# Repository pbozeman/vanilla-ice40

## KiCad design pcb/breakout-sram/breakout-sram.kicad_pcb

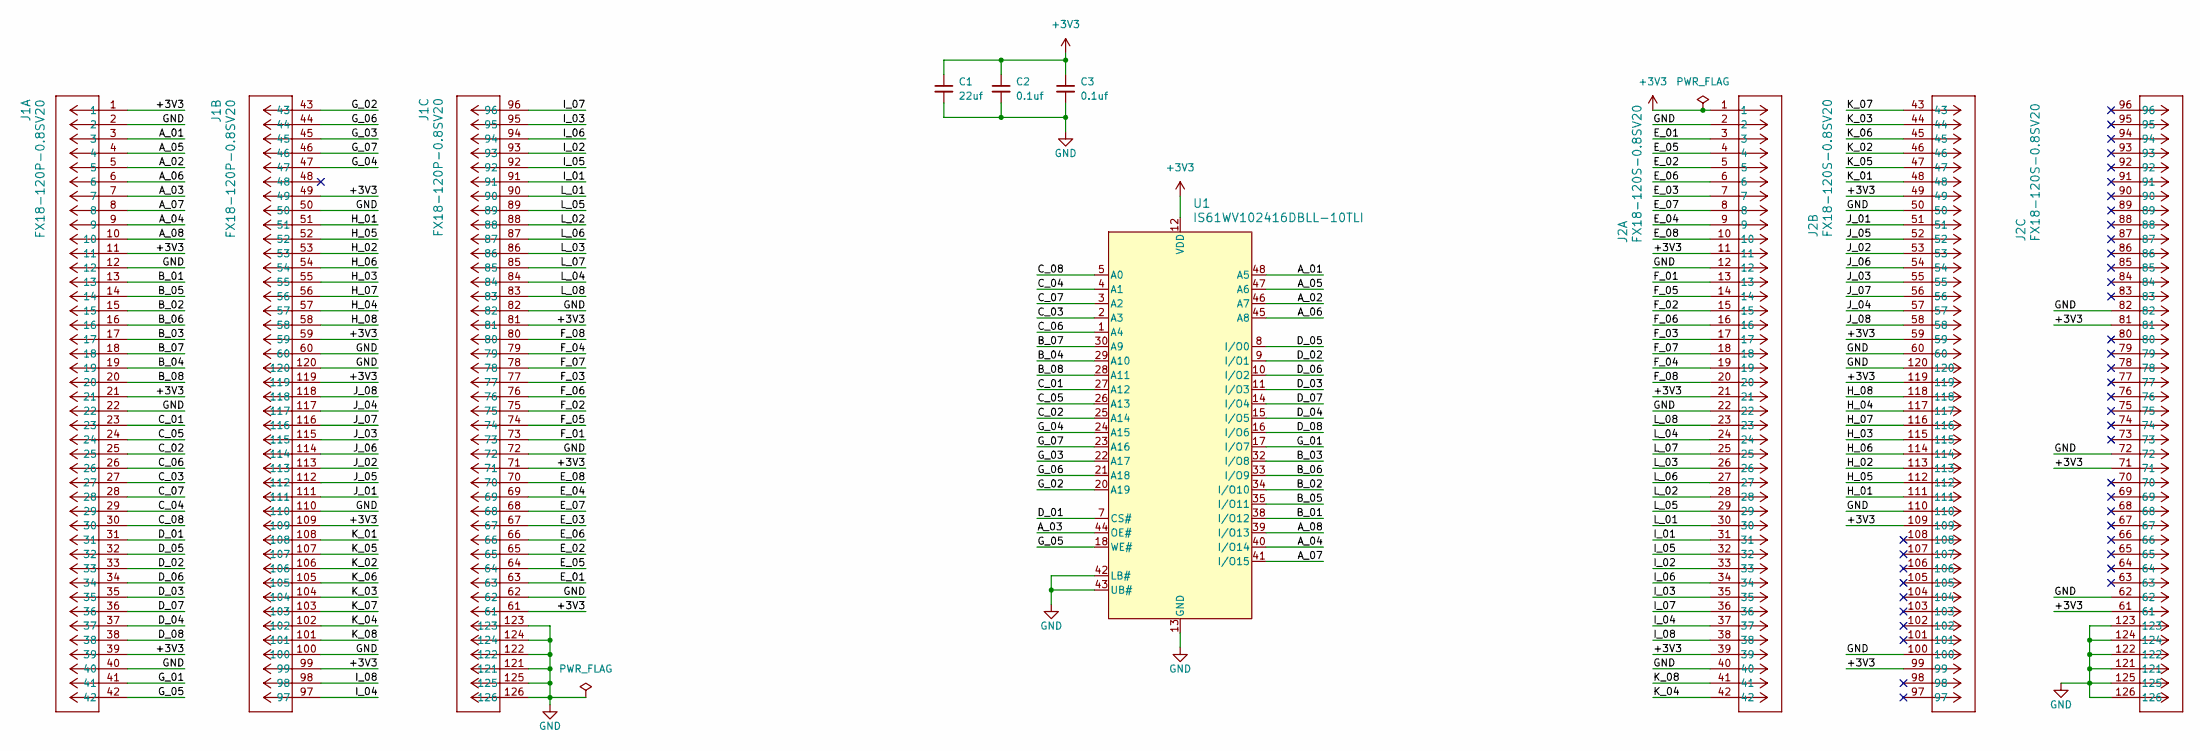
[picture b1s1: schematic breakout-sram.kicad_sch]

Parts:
C1: 22uf; C_0603_1608Metric; LCSC Part # C59461
C2, C3: 0.1uf; C_0402_1005Metric; LCSC Part # C1525
J1: FX18-120P-0.8SV20; CUSTOM_FX_120P-0.8SH20; Digi-Key Part Number H11865-ND
J2: FX18-120S-0.8SV20; CUSTOM_FX_120S-0.8SH20; Digi-Key Part Number H11867-ND
U1: IS61WV102416DBLL-10TLI; IS61WV102416DBLL-10TLI_ISI; LCSC Part # C1348726

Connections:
+3V3: C1.1, C2.1, C3.1, J1.1, J1.11, J1.21, J1.39, J1.49, J1.59, J1.61, J1.71, J1.81, J1.99, J1.109, J1.119, J2.1, J2.11, J2.21, J2.39, J2.49, J2.59, J2.61, J2.71, J2.81, J2.99, J2.109, J2.119, U1.12 (VDD), U1.36 (VDD)
/A_01: J1.3, U1.48 (A5)
/A_02: J1.5, U1.46 (A7)
/A_03: J1.7, U1.44 (OE#)
/A_04: J1.9, U1.40 (I/O14)
/A_05: J1.4, U1.47 (A6)
/A_06: J1.6, U1.45 (A8)
/A_07: J1.8, U1.41 (I/O15)
/A_08: J1.10, U1.39 (I/O13)
/B_01: J1.13, U1.38 (I/O12)
/B_02: J1.15, U1.34 (I/O10)
/B_03: J1.17, U1.32 (I/O8)
/B_04: J1.19, U1.29 (A10)
/B_05: J1.14, U1.35 (I/O11)
/B_06: J1.16, U1.33 (I/O9)
/B_07: J1.18, U1.30 (A9)
/B_08: J1.20, U1.28 (A11)
/C_01: J1.23, U1.27 (A12)
/C_02: J1.25, U1.25 (A14)
/C_03: J1.27, U1.2 (A3)
/C_04: J1.29, U1.4 (A1)
/C_05: J1.24, U1.26 (A13)
/C_06: J1.26, U1.1 (A4)
/C_07: J1.28, U1.3 (A2)
/C_08: J1.30, U1.5 (A0)
/D_01: J1.31, U1.7 (CS#)
/D_02: J1.33, U1.9 (I/O1)
/D_03: J1.35, U1.11 (I/O3)
/D_04: J1.37, U1.15 (I/O5)
/D_05: J1.32, U1.8 (I/O0)
/D_06: J1.34, U1.10 (I/O2)
/D_07: J1.36, U1.14 (I/O4)
/D_08: J1.38, U1.16 (I/O6)
/E_01: J1.63, J2.3
/E_02: J1.65, J2.5
/E_03: J1.67, J2.7
/E_04: J1.69, J2.9
/E_05: J1.64, J2.4
/E_06: J1.66, J2.6
/E_07: J1.68, J2.8
/E_08: J1.70, J2.10
/F_01: J1.73, J2.13
/F_02: J1.75, J2.15
/F_03: J1.77, J2.17
/F_04: J1.79, J2.19
/F_05: J1.74, J2.14
/F_06: J1.76, J2.16
/F_07: J1.78, J2.18
/F_08: J1.80, J2.20
/G_01: J1.41, U1.17 (I/O7)
/G_02: J1.43, U1.20 (A19)
/G_03: J1.45, U1.22 (A17)
/G_04: J1.47, U1.24 (A15)
/G_05: J1.42, U1.18 (WE#)
/G_06: J1.44, U1.21 (A18)
/G_07: J1.46, U1.23 (A16)
/H_01: J1.51, J2.111
/H_02: J1.53, J2.113
/H_03: J1.55, J2.115
/H_04: J1.57, J2.117
/H_05: J1.52, J2.112
/H_06: J1.54, J2.114
/H_07: J1.56, J2.116
/H_08: J1.58, J2.118
/I_01: J1.91, J2.31
/I_02: J1.93, J2.33
/I_03: J1.95, J2.35
/I_04: J1.97, J2.37
/I_05: J1.92, J2.32
/I_06: J1.94, J2.34
/I_07: J1.96, J2.36
/I_08: J1.98, J2.38
/J_01: J1.111, J2.51
/J_02: J1.113, J2.53
/J_03: J1.115, J2.55
/J_04: J1.117, J2.57
/J_05: J1.112, J2.52
/J_06: J1.114, J2.54
/J_07: J1.116, J2.56
/J_08: J1.118, J2.58
/K_01: J1.108, J2.48
/K_02: J1.106, J2.46
/K_03: J1.104, J2.44
/K_04: J1.102, J2.42
/K_05: J1.107, J2.47
/K_06: J1.105, J2.45
/K_07: J1.103, J2.43
/K_08: J1.101, J2.41
/L_01: J1.90, J2.30
/L_02: J1.88, J2.28
/L_03: J1.86, J2.26
/L_04: J1.84, J2.24
/L_05: J1.89, J2.29
/L_06: J1.87, J2.27
/L_07: J1.85, J2.25
/L_08: J1.83, J2.23
GND: C1.2, C2.2, C3.2, J1.2, J1.12, J1.22, J1.40, J1.50, J1.60, J1.62, J1.72, J1.82, J1.100, J1.110, J1.120, J1.121, J1.122, J1.123, J1.124, J1.125, J1.126, J2.2, J2.12, J2.22, J2.40, J2.50, J2.60, J2.62, J2.72, J2.82, J2.100, J2.110, J2.120, J2.121, J2.122, J2.123, J2.124, J2.125, J2.126, U1.13 (GND), U1.37 (GND), U1.42 (LB#), U1.43 (UB#)

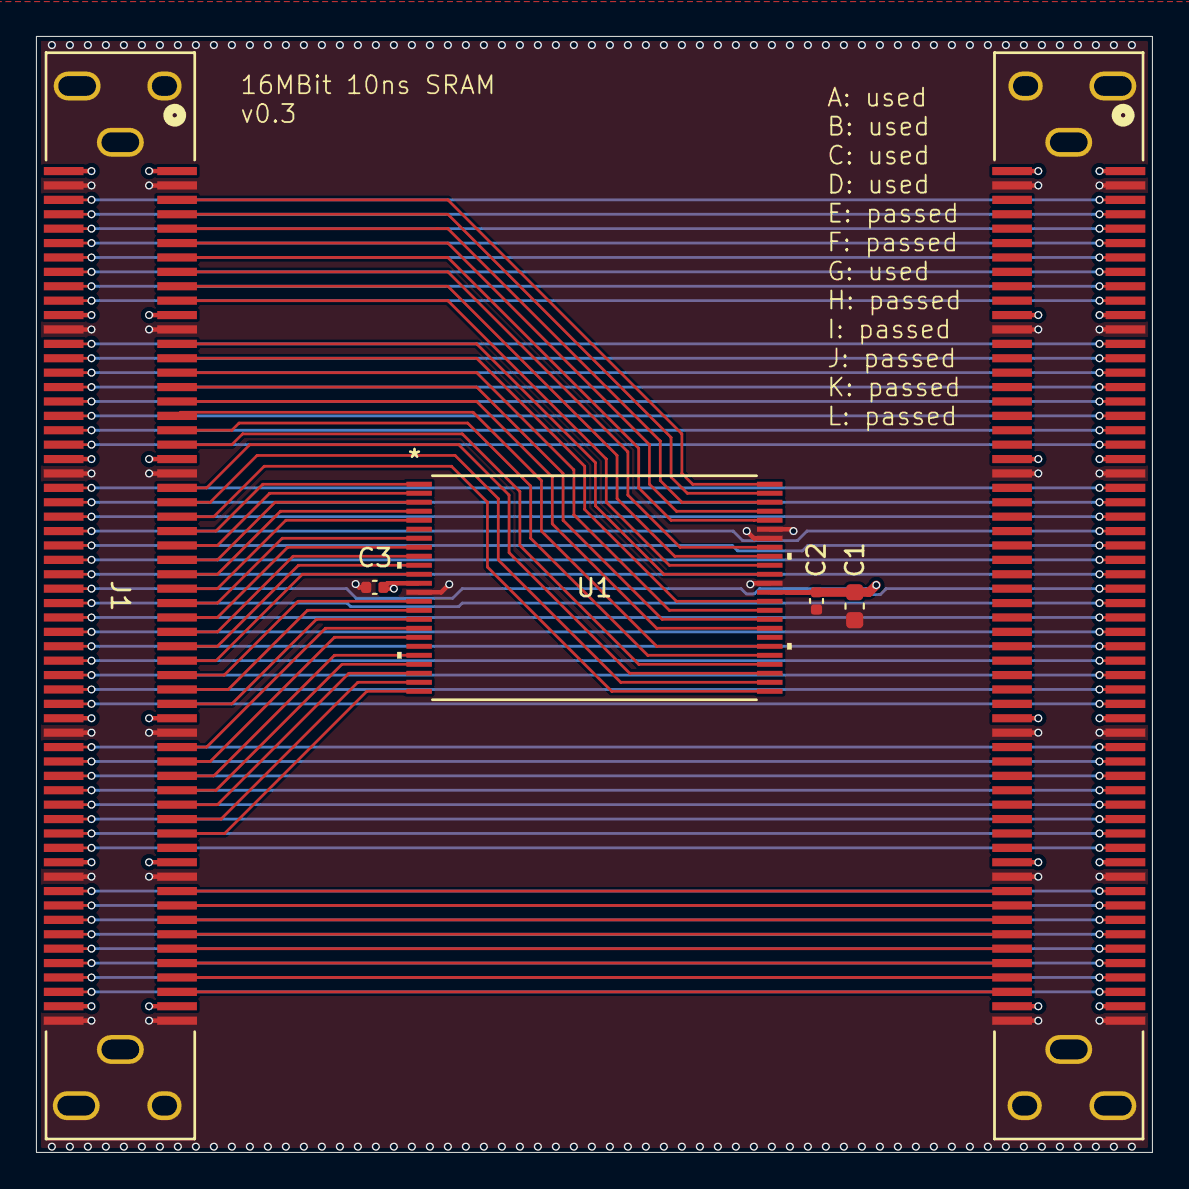
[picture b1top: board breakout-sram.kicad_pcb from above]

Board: 4 copper layers, 62.0 x 62.0 mm, 6 parts (0 on the bottom side), 97 nets.

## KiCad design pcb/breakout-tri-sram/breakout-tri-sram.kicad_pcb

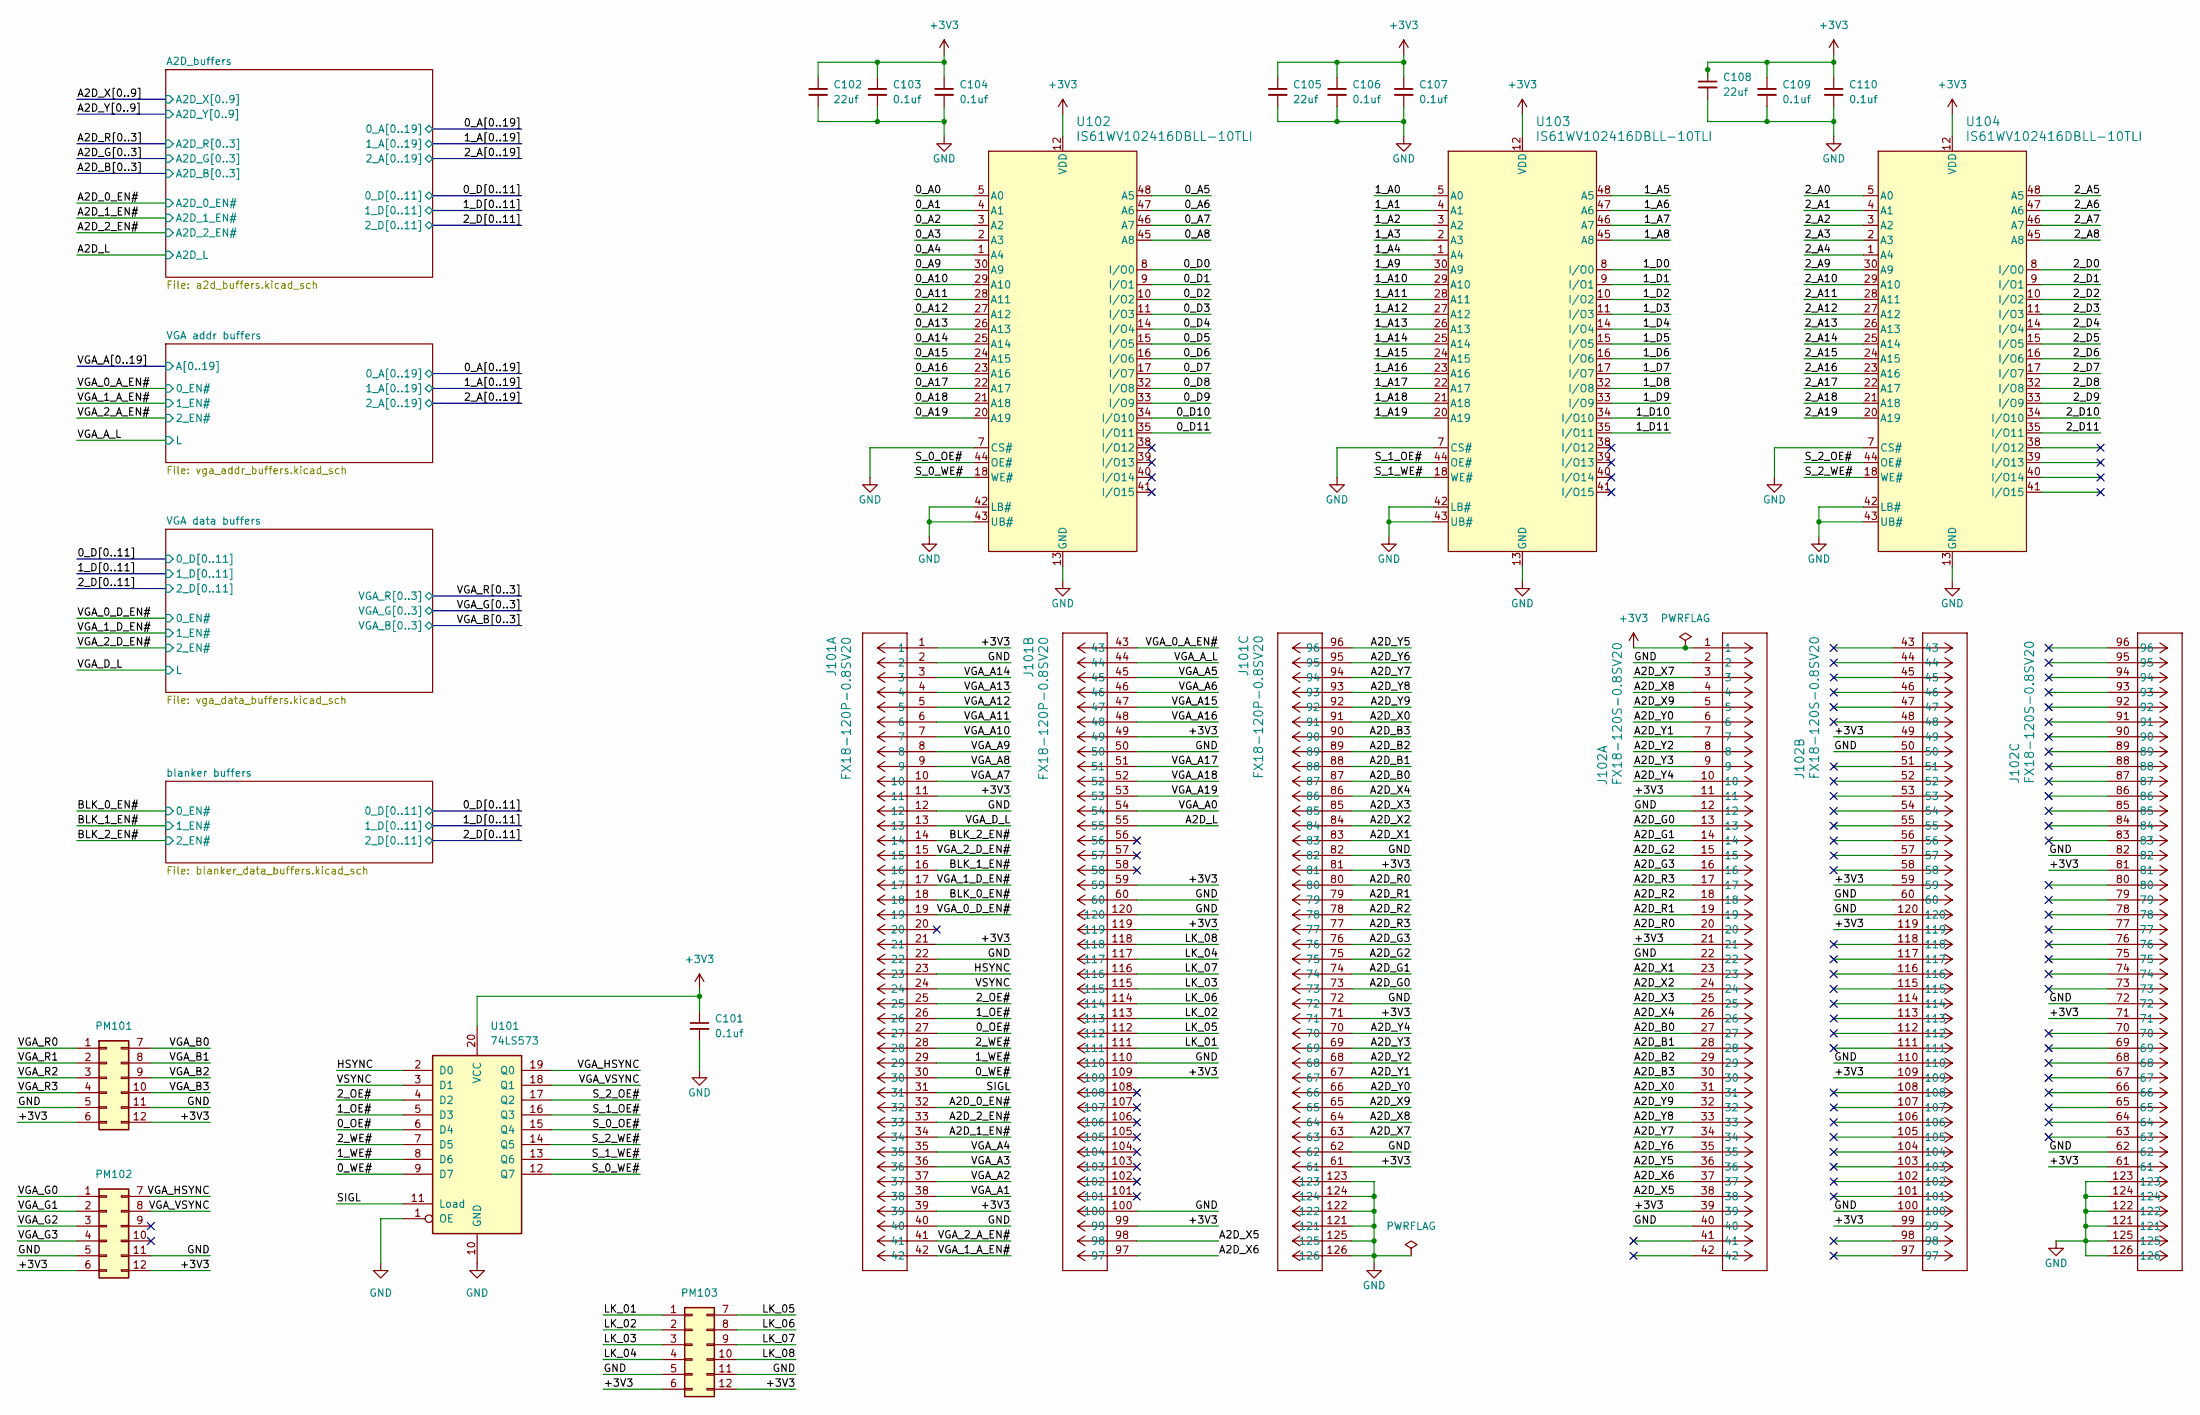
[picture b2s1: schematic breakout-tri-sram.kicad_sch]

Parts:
C101, C103, C104, C106, C107, C109, C110: 0.1uf; C_0402_1005Metric; LCSC Part # C1525
C102, C105, C108: 22uf; C_0603_1608Metric; LCSC Part # C59461
J101: FX18-120P-0.8SV20; CUSTOM_FX_120S-0.8SH20; Digi-Key Part Number H11865-ND
J102: FX18-120S-0.8SV20; CUSTOM_FX_120S-0.8SH20; Digi-Key Part Number H11867-ND
PM101, PM102, PM103: Conn_02x06_Top_Bottom; PMOD_12p_Horizontal; Digi-Key Part Number S5559-ND
U101: 74LS573; SSOP-20_4.4x6.5mm_P0.65mm; LCSC Part # C7194124
U102, U103, U104: IS61WV102416DBLL-10TLI; IS61WV102416DBLL-10TLI_ISI; LCSC Part # C1348726

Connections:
+3V3: C101.1, C102.1, C103.1, C104.1, C105.1, C106.1, C107.1, C108.1, C109.1, C110.1, J101.1, J101.11, J101.21, J101.39, J101.49, J101.59, J101.61, J101.71, J101.81, J101.99, J101.109, J101.119, J102.1, J102.11, J102.21, J102.39, J102.49, J102.59, J102.61, J102.71, J102.81, J102.99, J102.109, J102.119, PM101.6, PM101.12, PM102.6, PM102.12, PM103.6, PM103.12, U101.20 (VCC), U102.12 (VDD), U102.36 (VDD), U103.12 (VDD), U103.36 (VDD), U104.12 (VDD), U104.36 (VDD); also elsewhere on the board
/0_A0: U102.5 (A0); also elsewhere on the board
/0_A1: U102.4 (A1); also elsewhere on the board
/0_A2: U102.3 (A2); also elsewhere on the board
/0_A3: U102.2 (A3); also elsewhere on the board
/0_A4: U102.1 (A4); also elsewhere on the board
/0_A5: U102.48 (A5); also elsewhere on the board
/0_A6: U102.47 (A6); also elsewhere on the board
/0_A7: U102.46 (A7); also elsewhere on the board
/0_A8: U102.45 (A8); also elsewhere on the board
/0_A9: U102.30 (A9); also elsewhere on the board
/0_A10: U102.29 (A10); also elsewhere on the board
/0_A11: U102.28 (A11); also elsewhere on the board
/0_A12: U102.27 (A12); also elsewhere on the board
/0_A13: U102.26 (A13); also elsewhere on the board
/0_A14: U102.25 (A14); also elsewhere on the board
/0_A15: U102.24 (A15); also elsewhere on the board
/0_A16: U102.23 (A16); also elsewhere on the board
/0_A17: U102.22 (A17); also elsewhere on the board
/0_A18: U102.21 (A18); also elsewhere on the board
/0_A19: U102.20 (A19); also elsewhere on the board
/0_D0: U102.8 (I/O0); also elsewhere on the board
/0_D1: U102.9 (I/O1); also elsewhere on the board
/0_D2: U102.10 (I/O2); also elsewhere on the board
/0_D3: U102.11 (I/O3); also elsewhere on the board
/0_D4: U102.14 (I/O4); also elsewhere on the board
/0_D5: U102.15 (I/O5); also elsewhere on the board
/0_D6: U102.16 (I/O6); also elsewhere on the board
/0_D7: U102.17 (I/O7); also elsewhere on the board
/0_D8: U102.32 (I/O8); also elsewhere on the board
/0_D9: U102.33 (I/O9); also elsewhere on the board
/0_D10: U102.34 (I/O10); also elsewhere on the board
/0_D11: U102.35 (I/O11); also elsewhere on the board
/0_OE#: J101.27, U101.6 (D4)
/0_WE#: J101.30, U101.9 (D7)
/1_A0: U103.5 (A0); also elsewhere on the board
/1_A1: U103.4 (A1); also elsewhere on the board
/1_A2: U103.3 (A2); also elsewhere on the board
/1_A3: U103.2 (A3); also elsewhere on the board
/1_A4: U103.1 (A4); also elsewhere on the board
/1_A5: U103.48 (A5); also elsewhere on the board
/1_A6: U103.47 (A6); also elsewhere on the board
/1_A7: U103.46 (A7); also elsewhere on the board
/1_A8: U103.45 (A8); also elsewhere on the board
/1_A9: U103.30 (A9); also elsewhere on the board
/1_A10: U103.29 (A10); also elsewhere on the board
/1_A11: U103.28 (A11); also elsewhere on the board
/1_A12: U103.27 (A12); also elsewhere on the board
/1_A13: U103.26 (A13); also elsewhere on the board
/1_A14: U103.25 (A14); also elsewhere on the board
/1_A15: U103.24 (A15); also elsewhere on the board
/1_A16: U103.23 (A16); also elsewhere on the board
/1_A17: U103.22 (A17); also elsewhere on the board
/1_A18: U103.21 (A18); also elsewhere on the board
/1_A19: U103.20 (A19); also elsewhere on the board
/1_D0: U103.8 (I/O0); also elsewhere on the board
/1_D1: U103.9 (I/O1); also elsewhere on the board
/1_D2: U103.10 (I/O2); also elsewhere on the board
/1_D3: U103.11 (I/O3); also elsewhere on the board
/1_D4: U103.14 (I/O4); also elsewhere on the board
/1_D5: U103.15 (I/O5); also elsewhere on the board
/1_D6: U103.16 (I/O6); also elsewhere on the board
/1_D7: U103.17 (I/O7); also elsewhere on the board
/1_D8: U103.32 (I/O8); also elsewhere on the board
/1_D9: U103.33 (I/O9); also elsewhere on the board
/1_D10: U103.34 (I/O10); also elsewhere on the board
/1_D11: U103.35 (I/O11); also elsewhere on the board
/1_OE#: J101.26, U101.5 (D3)
/1_WE#: J101.29, U101.8 (D6)
/2_A0: U104.5 (A0); also elsewhere on the board
/2_A1: U104.4 (A1); also elsewhere on the board
/2_A2: U104.3 (A2); also elsewhere on the board
/2_A3: U104.2 (A3); also elsewhere on the board
/2_A4: U104.1 (A4); also elsewhere on the board
/2_A5: U104.48 (A5); also elsewhere on the board
/2_A6: U104.47 (A6); also elsewhere on the board
/2_A7: U104.46 (A7); also elsewhere on the board
/2_A8: U104.45 (A8); also elsewhere on the board
/2_A9: U104.30 (A9); also elsewhere on the board
/2_A10: U104.29 (A10); also elsewhere on the board
/2_A11: U104.28 (A11); also elsewhere on the board
/2_A12: U104.27 (A12); also elsewhere on the board
/2_A13: U104.26 (A13); also elsewhere on the board
/2_A14: U104.25 (A14); also elsewhere on the board
/2_A15: U104.24 (A15); also elsewhere on the board
/2_A16: U104.23 (A16); also elsewhere on the board
/2_A17: U104.22 (A17); also elsewhere on the board
/2_A18: U104.21 (A18); also elsewhere on the board
/2_A19: U104.20 (A19); also elsewhere on the board
/2_D0: U104.8 (I/O0); also elsewhere on the board
/2_D1: U104.9 (I/O1); also elsewhere on the board
/2_D2: U104.10 (I/O2); also elsewhere on the board
/2_D3: U104.11 (I/O3); also elsewhere on the board
/2_D4: U104.14 (I/O4); also elsewhere on the board
/2_D5: U104.15 (I/O5); also elsewhere on the board
/2_D6: U104.16 (I/O6); also elsewhere on the board
/2_D7: U104.17 (I/O7); also elsewhere on the board
/2_D8: U104.32 (I/O8); also elsewhere on the board
/2_D9: U104.33 (I/O9); also elsewhere on the board
/2_D10: U104.34 (I/O10); also elsewhere on the board
/2_D11: U104.35 (I/O11); also elsewhere on the board
/2_OE#: J101.25, U101.4 (D2)
/2_WE#: J101.28, U101.7 (D5)
/A2D_0_EN#: J101.32; also elsewhere on the board
/A2D_1_EN#: J101.34; also elsewhere on the board
/A2D_2_EN#: J101.33; also elsewhere on the board
/A2D_B0: J101.87, J102.27; also elsewhere on the board
/A2D_B1: J101.88, J102.28; also elsewhere on the board
/A2D_B2: J101.89, J102.29; also elsewhere on the board
/A2D_B3: J101.90, J102.30; also elsewhere on the board
/A2D_G0: J101.73, J102.13; also elsewhere on the board
/A2D_G1: J101.74, J102.14; also elsewhere on the board
/A2D_G2: J101.75, J102.15; also elsewhere on the board
/A2D_G3: J101.76, J102.16; also elsewhere on the board
/A2D_L: J101.55; also elsewhere on the board
/A2D_R0: J101.80, J102.20; also elsewhere on the board
/A2D_R1: J101.79, J102.19; also elsewhere on the board
/A2D_R2: J101.78, J102.18; also elsewhere on the board
/A2D_R3: J101.77, J102.17; also elsewhere on the board
/A2D_X0: J101.91, J102.31; also elsewhere on the board
/A2D_X1: J101.83, J102.23; also elsewhere on the board
/A2D_X2: J101.84, J102.24; also elsewhere on the board
/A2D_X3: J101.85, J102.25; also elsewhere on the board
/A2D_X4: J101.86, J102.26; also elsewhere on the board
/A2D_X5: J101.98, J102.38; also elsewhere on the board
/A2D_X6: J101.97, J102.37; also elsewhere on the board
/A2D_X7: J101.63, J102.3; also elsewhere on the board
/A2D_X8: J101.64, J102.4; also elsewhere on the board
/A2D_X9: J101.65, J102.5; also elsewhere on the board
/A2D_Y0: J101.66, J102.6; also elsewhere on the board
/A2D_Y1: J101.67, J102.7; also elsewhere on the board
/A2D_Y2: J101.68, J102.8; also elsewhere on the board
/A2D_Y3: J101.69, J102.9; also elsewhere on the board
/A2D_Y4: J101.70, J102.10; also elsewhere on the board
/A2D_Y5: J101.96, J102.36; also elsewhere on the board
/A2D_Y6: J101.95, J102.35; also elsewhere on the board
/A2D_Y7: J101.94, J102.34; also elsewhere on the board
/A2D_Y8: J101.93, J102.33; also elsewhere on the board
/A2D_Y9: J101.92, J102.32; also elsewhere on the board
/BLK_0_EN#: J101.18; also elsewhere on the board
/BLK_1_EN#: J101.16; also elsewhere on the board
/BLK_2_EN#: J101.14; also elsewhere on the board
/HSYNC: J101.23, U101.2 (D0)
/LK_01: J101.111, PM103.1
/LK_02: J101.113, PM103.2
/LK_03: J101.115, PM103.3
/LK_04: J101.117, PM103.4
/LK_05: J101.112, PM103.7
/LK_06: J101.114, PM103.8
/LK_07: J101.116, PM103.9
/LK_08: J101.118, PM103.10
/SIGL: J101.31, U101.11 (Load)
/S_0_OE#: U101.15 (Q4), U102.44 (OE#)
/S_0_WE#: U101.12 (Q7), U102.18 (WE#)
/S_1_OE#: U101.16 (Q3), U103.44 (OE#)
/S_1_WE#: U101.13 (Q6), U103.18 (WE#)
/S_2_OE#: U101.17 (Q2), U104.44 (OE#)
/S_2_WE#: U101.14 (Q5), U104.18 (WE#)
/VGA_0_A_EN#: J101.43; also elsewhere on the board
/VGA_0_D_EN#: J101.19; also elsewhere on the board
/VGA_1_A_EN#: J101.42; also elsewhere on the board
/VGA_1_D_EN#: J101.17; also elsewhere on the board
/VGA_2_A_EN#: J101.41; also elsewhere on the board
/VGA_2_D_EN#: J101.15; also elsewhere on the board
/VGA_A0: J101.54; also elsewhere on the board
/VGA_A1: J101.38; also elsewhere on the board
/VGA_A2: J101.37; also elsewhere on the board
/VGA_A3: J101.36; also elsewhere on the board
/VGA_A4: J101.35; also elsewhere on the board
/VGA_A5: J101.45; also elsewhere on the board
/VGA_A6: J101.46; also elsewhere on the board
/VGA_A7: J101.10; also elsewhere on the board
/VGA_A8: J101.9; also elsewhere on the board
/VGA_A9: J101.8; also elsewhere on the board
/VGA_A10: J101.7; also elsewhere on the board
/VGA_A11: J101.6; also elsewhere on the board
/VGA_A12: J101.5; also elsewhere on the board
/VGA_A13: J101.4; also elsewhere on the board
/VGA_A14: J101.3; also elsewhere on the board
/VGA_A15: J101.47; also elsewhere on the board
/VGA_A16: J101.48; also elsewhere on the board
/VGA_A17: J101.51; also elsewhere on the board
/VGA_A18: J101.52; also elsewhere on the board
/VGA_A19: J101.53; also elsewhere on the board
/VGA_A_L: J101.44; also elsewhere on the board
/VGA_B0: PM101.7; also elsewhere on the board
/VGA_B1: PM101.8; also elsewhere on the board
/VGA_B2: PM101.9; also elsewhere on the board
/VGA_B3: PM101.10; also elsewhere on the board
/VGA_D_L: J101.13; also elsewhere on the board
/VGA_G0: PM102.1; also elsewhere on the board
/VGA_G1: PM102.2; also elsewhere on the board
/VGA_G2: PM102.3; also elsewhere on the board
/VGA_G3: PM102.4; also elsewhere on the board
/VGA_HSYNC: PM102.7, U101.19 (Q0)
/VGA_R0: PM101.1; also elsewhere on the board
/VGA_R1: PM101.2; also elsewhere on the board
/VGA_R2: PM101.3; also elsewhere on the board
/VGA_R3: PM101.4; also elsewhere on the board
/VGA_VSYNC: PM102.8, U101.18 (Q1)
/VSYNC: J101.24, U101.3 (D1)
GND: C101.2, C102.2, C103.2, C104.2, C105.2, C106.2, C107.2, C108.2, C109.2, C110.2, J101.2, J101.12, J101.22, J101.40, J101.50, J101.60, J101.62, J101.72, J101.82, J101.100, J101.110, J101.120, J101.121, J101.122, J101.123, J101.124, J101.125, J101.126, J102.2, J102.12, J102.22, J102.40, J102.50, J102.60, J102.62, J102.72, J102.82, J102.100, J102.110, J102.120, J102.121, J102.122, J102.123, J102.124, J102.125, J102.126, PM101.5, PM101.11, PM102.5, PM102.11, PM103.5, PM103.11, U101.1 (OE), U101.10 (GND), U102.7 (CS#), U102.13 (GND), U102.37 (GND), U102.42 (LB#), U102.43 (UB#), U103.7 (CS#), U103.13 (GND), U103.37 (GND), U103.42 (LB#), U103.43 (UB#), U104.7 (CS#), U104.13 (GND), U104.37 (GND), U104.42 (LB#), U104.43 (UB#); also elsewhere on the board

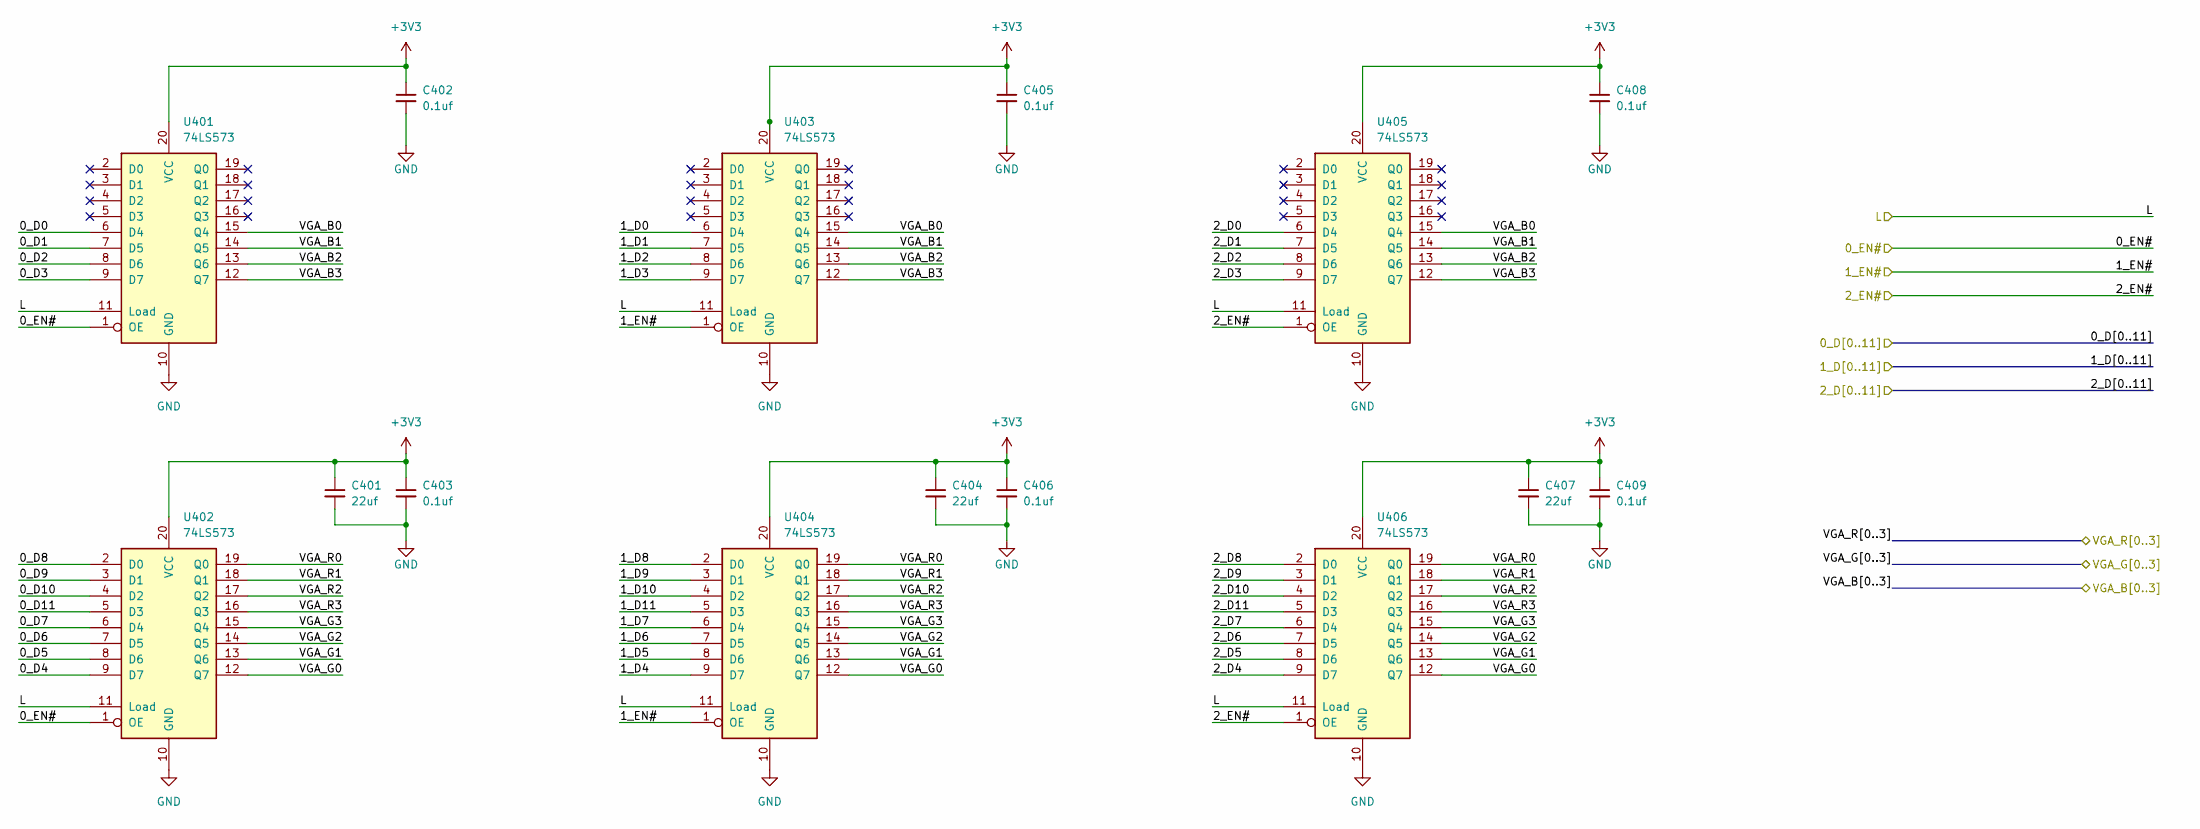
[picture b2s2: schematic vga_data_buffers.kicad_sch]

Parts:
C401, C404, C407: 22uf; C_0603_1608Metric; LCSC Part # C59461
C402, C403, C405, C406, C408, C409: 0.1uf; C_0402_1005Metric; LCSC Part # C1525
U401, U402, U403, U404, U405, U406: 74LS573; SSOP-20_4.4x6.5mm_P0.65mm; LCSC Part # C7194124

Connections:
+3V3: C401.1, C402.1, C403.1, C404.1, C405.1, C406.1, C407.1, C408.1, C409.1, U401.20 (VCC), U402.20 (VCC), U403.20 (VCC), U404.20 (VCC), U405.20 (VCC), U406.20 (VCC); also elsewhere on the board
/0_D0: U401.6 (D4); also elsewhere on the board
/0_D1: U401.7 (D5); also elsewhere on the board
/0_D2: U401.8 (D6); also elsewhere on the board
/0_D3: U401.9 (D7); also elsewhere on the board
/0_D4: U402.9 (D7); also elsewhere on the board
/0_D5: U402.8 (D6); also elsewhere on the board
/0_D6: U402.7 (D5); also elsewhere on the board
/0_D7: U402.6 (D4); also elsewhere on the board
/0_D8: U402.2 (D0); also elsewhere on the board
/0_D9: U402.3 (D1); also elsewhere on the board
/0_D10: U402.4 (D2); also elsewhere on the board
/0_D11: U402.5 (D3); also elsewhere on the board
/1_D0: U403.6 (D4); also elsewhere on the board
/1_D1: U403.7 (D5); also elsewhere on the board
/1_D2: U403.8 (D6); also elsewhere on the board
/1_D3: U403.9 (D7); also elsewhere on the board
/1_D4: U404.9 (D7); also elsewhere on the board
/1_D5: U404.8 (D6); also elsewhere on the board
/1_D6: U404.7 (D5); also elsewhere on the board
/1_D7: U404.6 (D4); also elsewhere on the board
/1_D8: U404.2 (D0); also elsewhere on the board
/1_D9: U404.3 (D1); also elsewhere on the board
/1_D10: U404.4 (D2); also elsewhere on the board
/1_D11: U404.5 (D3); also elsewhere on the board
/2_D0: U405.6 (D4); also elsewhere on the board
/2_D1: U405.7 (D5); also elsewhere on the board
/2_D2: U405.8 (D6); also elsewhere on the board
/2_D3: U405.9 (D7); also elsewhere on the board
/2_D4: U406.9 (D7); also elsewhere on the board
/2_D5: U406.8 (D6); also elsewhere on the board
/2_D6: U406.7 (D5); also elsewhere on the board
/2_D7: U406.6 (D4); also elsewhere on the board
/2_D8: U406.2 (D0); also elsewhere on the board
/2_D9: U406.3 (D1); also elsewhere on the board
/2_D10: U406.4 (D2); also elsewhere on the board
/2_D11: U406.5 (D3); also elsewhere on the board
/VGA_0_D_EN#: U401.1 (OE), U402.1 (OE); also elsewhere on the board
/VGA_1_D_EN#: U403.1 (OE), U404.1 (OE); also elsewhere on the board
/VGA_2_D_EN#: U405.1 (OE), U406.1 (OE); also elsewhere on the board
/VGA_B0: U401.15 (Q4), U403.15 (Q4), U405.15 (Q4); also elsewhere on the board
/VGA_B1: U401.14 (Q5), U403.14 (Q5), U405.14 (Q5); also elsewhere on the board
/VGA_B2: U401.13 (Q6), U403.13 (Q6), U405.13 (Q6); also elsewhere on the board
/VGA_B3: U401.12 (Q7), U403.12 (Q7), U405.12 (Q7); also elsewhere on the board
/VGA_D_L: U401.11 (Load), U402.11 (Load), U403.11 (Load), U404.11 (Load), U405.11 (Load), U406.11 (Load); also elsewhere on the board
/VGA_G0: U402.12 (Q7), U404.12 (Q7), U406.12 (Q7); also elsewhere on the board
/VGA_G1: U402.13 (Q6), U404.13 (Q6), U406.13 (Q6); also elsewhere on the board
/VGA_G2: U402.14 (Q5), U404.14 (Q5), U406.14 (Q5); also elsewhere on the board
/VGA_G3: U402.15 (Q4), U404.15 (Q4), U406.15 (Q4); also elsewhere on the board
/VGA_R0: U402.19 (Q0), U404.19 (Q0), U406.19 (Q0); also elsewhere on the board
/VGA_R1: U402.18 (Q1), U404.18 (Q1), U406.18 (Q1); also elsewhere on the board
/VGA_R2: U402.17 (Q2), U404.17 (Q2), U406.17 (Q2); also elsewhere on the board
/VGA_R3: U402.16 (Q3), U404.16 (Q3), U406.16 (Q3); also elsewhere on the board
GND: C401.2, C402.2, C403.2, C404.2, C405.2, C406.2, C407.2, C408.2, C409.2, U401.10 (GND), U402.10 (GND), U403.10 (GND), U404.10 (GND), U405.10 (GND), U406.10 (GND); also elsewhere on the board
